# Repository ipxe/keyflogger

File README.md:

# USB keyboard/mouse injector

The `keyflogger` device allows one host computer to inject keystrokes
and mouse movements into another.  It can be used to remotely control
a computer that does not provide any software mechanism for remote
access.

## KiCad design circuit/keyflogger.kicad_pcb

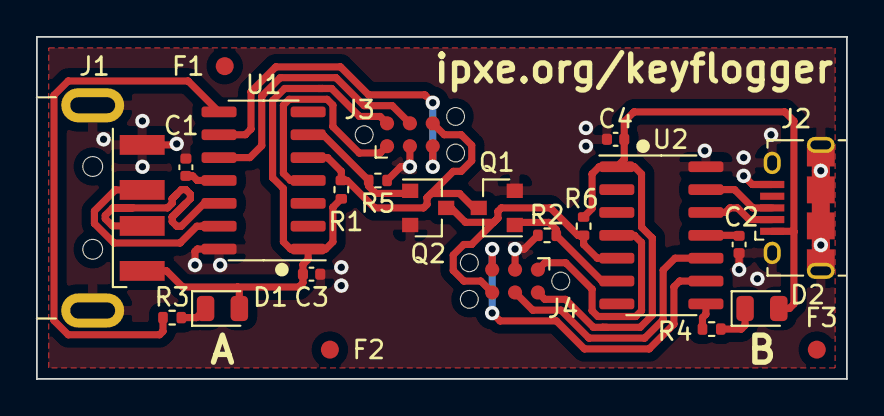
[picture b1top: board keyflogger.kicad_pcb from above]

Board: 2 copper layers, 45.0 x 19.0 mm, 23 parts (0 on the bottom side), 23 nets.

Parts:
C1, C2, C3, C4: 470n; C_0402_1005Metric
D1, D2: Red 2mA; LED_0805_2012Metric
F1, F2, F3: Fiducial; Fiducial_1mm_Mask2mm
J1: USB_A; USB_A_CNCTech_1001-011-01101_Horizontal
J2: USB_B_Micro; USB_Micro-B_Amphenol_10118194_Horizontal
J3, J4: Conn_PIC_ICSP_ICD; Tag-Connect_TC2030-IDC-NL_2x03_P1.27mm_Vertical
Q1, Q2: 2N7002; SOT-23
R1, R2, R5, R6: 4K7; R_0402_1005Metric
R3, R4: 1K5; R_0402_1005Metric
U1, U2: PIC16F1454-IP; SOIC-14_3.9x8.7mm_P1.27mm

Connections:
/ICSPCLK1: J3.5, U1.9
/ICSPCLK2: J4.5, U2.9
/ICSPDAT1: J3.4, U1.10
/ICSPDAT2: J4.4, U2.10
/RX1: J3.6, Q1.3, R1.1, U1.5
/RX2: J4.6, Q2.3, R6.2, U2.5
/USB1_D+: J1.3, U1.13
/USB1_D-: J1.2, U1.12
/USB2_D+: J2.3, U2.13
/USB2_D-: J2.2, U2.12
/VUSB1: C1.1, U1.11
/VUSB2: C2.2, U2.11
/~LED1~: R3.2, U1.8
/~LED2~: R4.2, U2.8
/~MCLR~_VPP1: J3.1, U1.4
/~MCLR~_VPP2: J4.1, U2.4
/~TX1~: Q2.1, R5.2, U1.6
/~TX2~: Q1.1, R2.1, U2.6
GND: C1.2, C2.1, C3.2, C4.2, J1.4, J1.5, J2.5, J2.6, J3.3, J4.3, Q1.2, Q2.2, R2.2, R5.1, U1.14, U2.14
unnamed: D1.1, R3.1
unnamed: D2.1, R4.1
VDD1: C3.1, D1.2, J1.1, J3.2, R1.2, U1.1
VDD2: C4.1, D2.2, J2.1, J4.2, R6.1, U2.1

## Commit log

2021-02-24 circuit: Add git filter for kicad project files
    kicad project (.pro) files contain "last updated" fields that are
    irritating for version control. Mark these files to be filtered via
    the "kicad_project" filter, which can be defined using:
    git config --global filter.kicad_project.clean \
    "sed -e '/^update=/d; /^last_client=/d;'"
2021-02-24 circuit: Add initial sketch of circuit design
2021-02-25 circuit: Add diodes to prevent back powering via nMCLR
2021-02-25 circuit: Add MOSFETs to prevent back powering via SCL/SDA
    Add an I2C bidirectional level shifter (based on Philips application
    note AN97055) in each power domain in order to prevent back powering
    via the SCL/SDA pins.
2021-02-25 circuit: Label remaining signals of interest
2021-02-26 circuit: Reroute status LED to pin 7 to simplify PCB routing
2021-02-26 circuit: Use Tag-Connect for in-system programming connector
2021-02-26 circuit: Use USB A plug for one external connection
    The circuit should fit within an off-the-shelf USB key enclosure, and
    so can use a USB A plug and only one USB micro B socket.
2021-02-26 circuit: Add initial sketch of PCB layout
2021-02-26 circuit: Add 1M resistors to prevent VDDx from floating
    Ensure that the I2C MOSFET gates are not left floating (and hence
    potentially failing to isolate) when power is disconnected.
2021-03-07 circuit: Use two separate ICSP connectors
    Programming two (identical) PICs in parallel via a single ICSP
    connector does work. However, the requirement to avoid back powering
    via the nMCLR/VPP pin is cumbersome to overcome: high-voltage
    programming requires the programmer to be able to drive nMCLR/VPP to
    at least 8.0V (thereby preventing the use of a common cathode diode)
    while low-voltage programming requires the programmer to be able to
2021-03-07 circuit: Add front ground plane
2021-03-25 firmware: Add stub firmware implementation
    Add a basic "hello world" firmware capable of enumerating as a USB HID
    device compatible with a boot keyboard, and sending (empty) HID
    reports.
2021-03-25 firmware: Allow status reporting via LED with a single instruction
    Redefine the status LED internal state to allow both activity and
    error status to be reported using a single "bsf" instruction, with an
    error now displayed as a series of slow blinks and taking priority
    over any concurrent activity blinks.
2021-03-25 circuit: Add 3D model for micro USB connector
2021-03-25 firmware: Initialise status LED subsystem first
    The LED subsystem has no further dependencies and should therefore be
    initialised first, in order to allow subsequent subsystems to report
    errors.
2021-03-25 circuit: Switch to using the UART to provide the data channel
    The PICs do not provide internal pull-ups on the I2C SCL/SDA pins,
    which would increase the external component count for the data channel
    to 10 parts in total (4x MOSFETs, 4x pull-up resistors, 2x pull-down
    resistors).
    Switch to using the UART, which requires only 6 external components
    (2x MOSFETs, 2x pull-up resistors, 2x pull-down resistors) and has the
2021-03-25 circuit: Add 3D model for USB A connector
2021-03-25 firmware: Use a UART transmit ring buffer
    Allow for the UART to be used for non-debug messages by providing a
    transmit ring buffer that can be filled without waiting for the
    transmission to complete.
    Rewrite USB debugging to use whole-line messages, in order to fit
    within the expected communication protocol.
2021-03-25 firmware: Add stub UART receive datapath
2021-04-02 firmware: Fill EP2/EP3 IN buffers via UART
    Accept commands comprising an initial "K" or "M" to select the
    keyboard or mouse endpoint, followed by sixteen hex digits to populate
    the corresponding HID report.
2021-04-03 firmware: Add mouse descriptors
2021-04-04 firmware: Add interrupt OUT endpoints
2021-04-04 firmware: Ignore received debug messages
2021-04-04 firmware: Always send initial '\n' even in non-debug builds
2021-04-04 firmware: Use a data stack and scratch registers
    Simplify the internal API by defining FSR1 to be a data stack pointer
    and allocating scratch registers within the common data area for use
    by any function.
2021-04-04 firmware: Zero-pad reports received via interrupt OUT endpoints
    USB HID reports delivered via an interrupt OUT endpoint include an
    initial report ID byte, if the device includes a report ID anywhere
    within its report descriptor. Report ID zero is reserved and may not
    be used.
    The Linux hidraw driver unconditionally requires an initial report ID
    byte in data written to /dev/hidrawN, with the documentation stating
2021-04-05 firmware: Refactor and reduce code duplication
    Separate out the code handling the inter-IC communication protocol
    from the UART and USB device driver code, and provide a shared
    function for refilling any of the interrupt endpoints.
2021-04-05 circuit: Update LED labels to reflect functional symmetry
    The firmware is identical on each side, and the device may be used in
    whichever orientation is more physically convenient. Update the LED
    labels to reflect this symmetry.
2021-04-05 doc: Add copy of GPL text
2021-04-05 doc: Add stub documentation
2021-04-05 firmware: Update to requested product ID code
2021-04-05 udev: Add udev rules
    Add udev rules to create /dev/keyflogger/{keyboard,mouse} and
    /dev/keyflogger/<usb-path>/{keyflogger,mouse}.
2021-04-05 circuit: Automate generation of PCB fabrication files
2021-04-06 circuit: Add fiducial markers
2021-04-06 circuit: Add solder paste layer to fabrication outputs
2021-04-06 circuit: Add bill of materials
2021-04-06 circuit: Update bill of materials for Seeed OPL
2021-04-07 circuit: Add PCB assembly outputs
2021-04-07 circuit: Tidy up fabrication and assembly output files
2021-04-07 circuit: Clean up assembly diagram
2021-04-07 circuit: Add title block to PCB diagrams
2021-04-07 circuit: Add silkscreen orientation markers for PIC ICs
2021-04-07 circuit: Update fabrication files to match Seeed guidelines
2021-04-07 circuit: Use updated SnapEDA model for USB A connector
2021-04-17 firmware: Mark USB product ID as formally assigned
2021-05-25 firmware: Preserve all registers in uart_tx_sync
2021-05-25 firmware: Wait for transmitter to become idle in uart_tx_sync
    Ensure that data has been physically transmitted before returning from
    uart_tx_sync, to allow for use in situations where the CPU is about to
    enter sleep mode.
2021-05-25 firmware: Handle USB suspend
    Handle USB suspend by dropping to a minimal power state with all
    peripherals and interrupts disabled (other than the ability to detect
    USB bus activity).
